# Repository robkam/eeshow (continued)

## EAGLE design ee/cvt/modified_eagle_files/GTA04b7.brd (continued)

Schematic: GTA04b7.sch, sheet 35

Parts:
P3401: BEAGLEBOARD
P3501: FH23-39S; FH23-39S-0.3SHW(0.5)

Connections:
BB-1V8: P3401.J5$2 (VIO_1V8); also elsewhere on the board
BB-3V3: P3401.J5$1 (3.3V), P3501.31, P3501.32; also elsewhere on the board
BB-5V: P3401.J4$1 (DC_5V), P3401.J4$2 (DC_5V), P3501.37, P3501.38, P3501.39; also elsewhere on the board
BB-DSS0: P3401.J4$4 (DATA0), P3501.1
BB-DSS1: P3401.J4$3 (DATA1), P3501.2
BB-DSS2: P3401.J4$6 (DATA2), P3501.3
BB-DSS3: P3401.J4$5 (DATA3), P3501.4
BB-DSS4: P3401.J4$8 (DATA4), P3501.5
BB-DSS5: P3401.J4$7 (DATA5), P3501.6
BB-DSS6: P3401.J5$15 (DATA6), P3501.7
BB-DSS7: P3401.J5$9 (DATA7), P3501.8
BB-DSS8: P3401.J5$11 (DATA8), P3501.9
BB-DSS9: P3401.J5$13 (DATA9), P3501.10
BB-DSS10: P3401.J4$10 (DATA10), P3501.11
BB-DSS11: P3401.J4$16 (DATA11), P3501.12
BB-DSS12: P3401.J4$9 (DATA12), P3501.13
BB-DSS13: P3401.J5$10 (DATA13), P3501.14
BB-DSS14: P3401.J4$12 (DATA14), P3501.15
BB-DSS15: P3401.J5$7 (DATA15), P3501.16
BB-DSS16: P3401.J5$8 (DATA16), P3501.17
BB-DSS17: P3401.J5$5 (DATA17), P3501.18
BB-DSS18: P3401.J5$6 (DATA18), P3501.19
BB-DSS19: P3401.J4$13 (DATA19), P3501.20
BB-DSS20: P3401.J5$3 (DATA20), P3501.21
BB-DSS21: P3401.J5$4 (DATA21), P3501.22
BB-DSS22: P3401.J4$14 (DATA22), P3501.23
BB-DSS23: P3401.J4$11 (DATA23), P3501.24
BB-DSSCK: P3401.J5$16 (CLK), P3501.27
BB-DSSDE: P3401.J5$17 (DEN), P3501.28
BB-DSSHS: P3401.J5$18 (HSYNC), P3501.25
BB-DSSVS: P3401.J4$17 (VSYNC), P3501.26
BB-I2C3SCL: P3401.J5$14 (I2C3SCL), P3501.30
BB-I2C3SDA: P3401.J4$15 (I2C3SDA), P3501.29
GND4: P3401.J4$19 (GND), P3401.J4$20 (GND), P3401.J5$19 (GND), P3401.J5$20 (GND), P3501.33, P3501.34, P3501.35, P3501.36; also elsewhere on the board

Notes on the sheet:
P2402
BB-XM Adapter (DISP)
(c) 2014 Golden Delicious Computers GmbH&Co. KG. Licensed under CC-BY-SA.
V2b
reverse?
check visually during layout phase

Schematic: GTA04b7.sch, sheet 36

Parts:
P3601: FH23-39S; FH23-39S-0.3SHW(0.5)
P3602: BEAGLEBOARD-XM-CAMERA; BEAGLEBOARD-XM-CAM

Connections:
BB-3V3: P3601.1, P3602.P10$24 (3V3), P3602.P10$25 (3V3), P3602.P10$26 (3V3); also elsewhere on the board
GND4: P3601.22, P3601.38, P3601.39, P3602.P10$4 (GND), P3602.P10$14 (GND), P3602.P10$20 (GND), P3602.P10$22 (GND), P3602.P10$28 (GND), P3602.P10$33 (GND), P3602.P10$34 (GND); also elsewhere on the board
unnamed: P3601.37, P3602.P10$30 (VAUX3), P3602.P10$32 (VAUX3)
unnamed: P3601.36, P3602.P10$16 (VAUX4), P3602.P10$18 (VAUX4)
unnamed: P3601.4, P3602.P10$27 (PCLK)
unnamed: P3601.5, P3602.P10$23 (D0)
unnamed: P3601.6, P3602.P10$21 (D1)
unnamed: P3601.7, P3602.P10$19 (D2)
unnamed: P3601.8, P3602.P10$17 (D3)
unnamed: P3601.9, P3602.P10$15 (D4)
unnamed: P3601.10, P3602.P10$13 (D5)
unnamed: P3601.11, P3602.P10$11 (D6)
unnamed: P3601.12, P3602.P10$9 (D7)
unnamed: P3601.13, P3602.P10$7 (D8)
unnamed: P3601.14, P3602.P10$5 (D9)
unnamed: P3601.15, P3602.P10$3 (D10)
unnamed: P3601.16, P3602.P10$1 (D11)
unnamed: P3601.3, P3602.P10$29 (HS)
unnamed: P3601.17, P3602.P10$2 (CLKA)
unnamed: P3601.18, P3602.P10$6 (I2C2-SDA)
unnamed: P3601.19, P3602.P10$8 (I2C2-SCL)
unnamed: P3601.20, P3602.P10$10 (FLD)
unnamed: P3601.21, P3602.P10$12 (WEN)

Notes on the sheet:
P2403
BB-XM Adapter (CAM)
(c) 2014 Golden Delicious Computers GmbH&Co. KG. Licensed under CC-BY-SA.
V2b
reverse?
check visually during layout phase

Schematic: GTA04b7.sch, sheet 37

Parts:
N3701, N3702, N3703: 15015-0439; NONE
N3704: N900 case assembly; NONE
N3705: N97-CAMERA-HOLE; N97-CAMERA-SPACE
N3706: headset jack; NONE
N3707: STENCIL-TOP; GDC-STENCIL
N3708: STENCIL-BOTTOM; GDC-STENCIL

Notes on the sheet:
No-Solder Components
(c) 2014 Golden Delicious Computers GmbH&Co. KG. Licensed under CC-BY-SA.
V2b
Molex Jumper cables to connect BB-XM-Adapter to Uppwer board
CPU
DISP
CAM

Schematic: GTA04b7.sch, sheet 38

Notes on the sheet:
Table of Contents
(c) 2015 Golden Delicious Computers GmbH&Co. KG. Licensed under CC-BY-SA.
V2b
1. Buttons 2. OTG port 3. Charger / OTG booster 4. Modem Power 5. Fuel Gauge 6. 3G/4G Modem + SIM 7. Dual SIM Switch 8. Antenna Connections 9. WLAN + Bluetooth + FM 10. Sensors 11. Audio: Codec 12. Audio: Headset & Microphone 13. ECI (remote control) 14. Audio: Handsfree 15. Misc on Lower Board 16.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

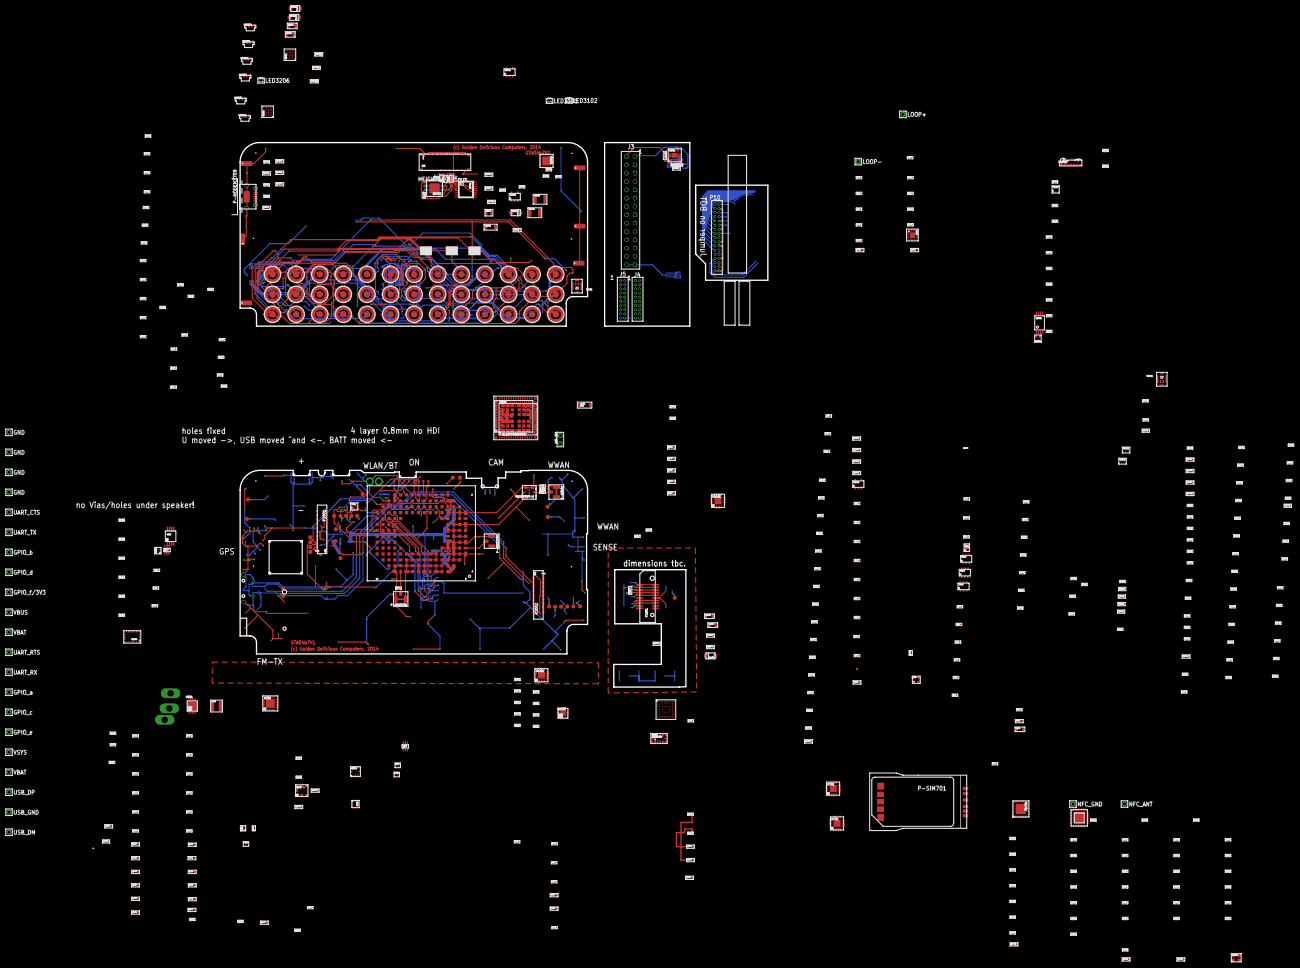
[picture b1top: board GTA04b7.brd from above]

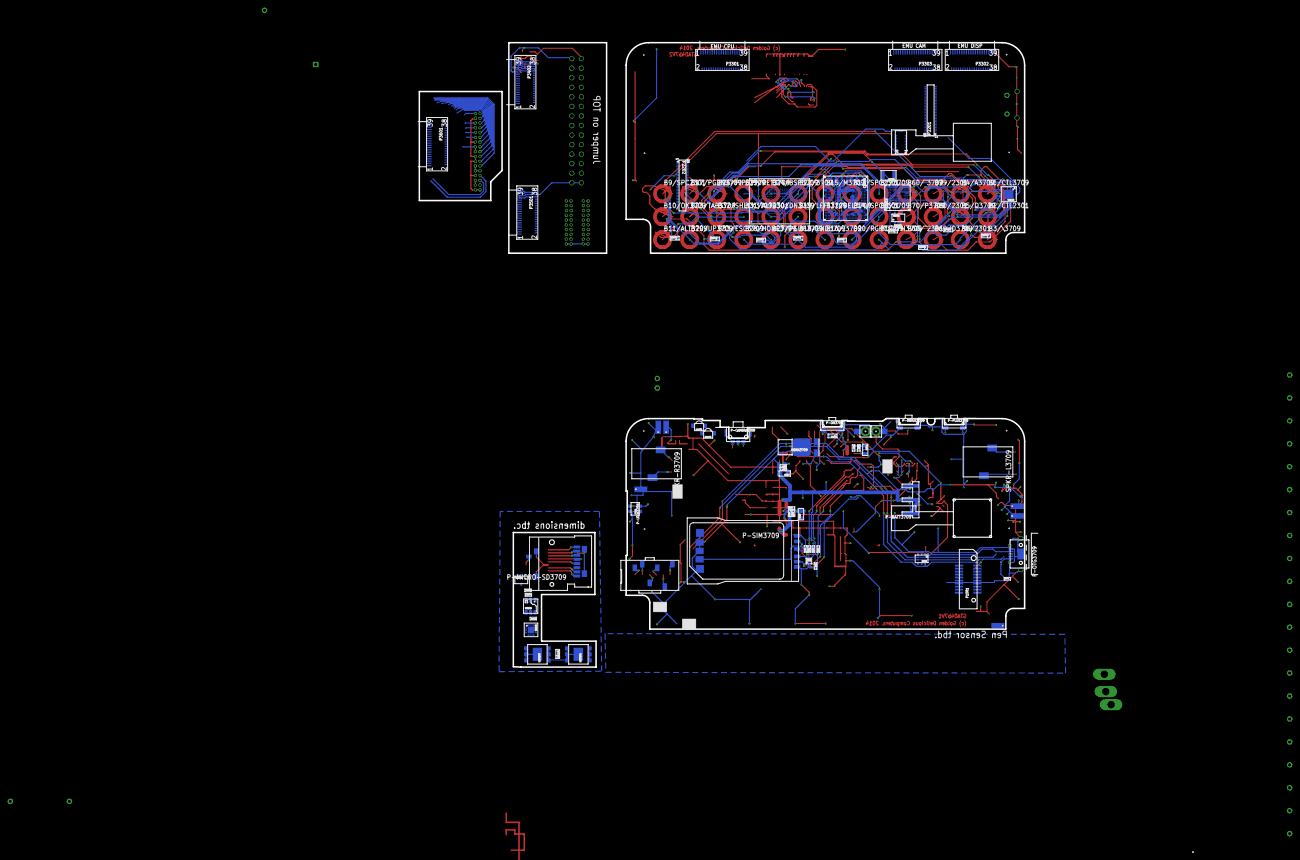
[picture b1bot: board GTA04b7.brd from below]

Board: 4 copper layers, 618 parts (86 on the bottom side), 530 nets.

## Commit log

2020-09-18 Add lib namespace for kicad 5
2021-01-28 add .gitignore
